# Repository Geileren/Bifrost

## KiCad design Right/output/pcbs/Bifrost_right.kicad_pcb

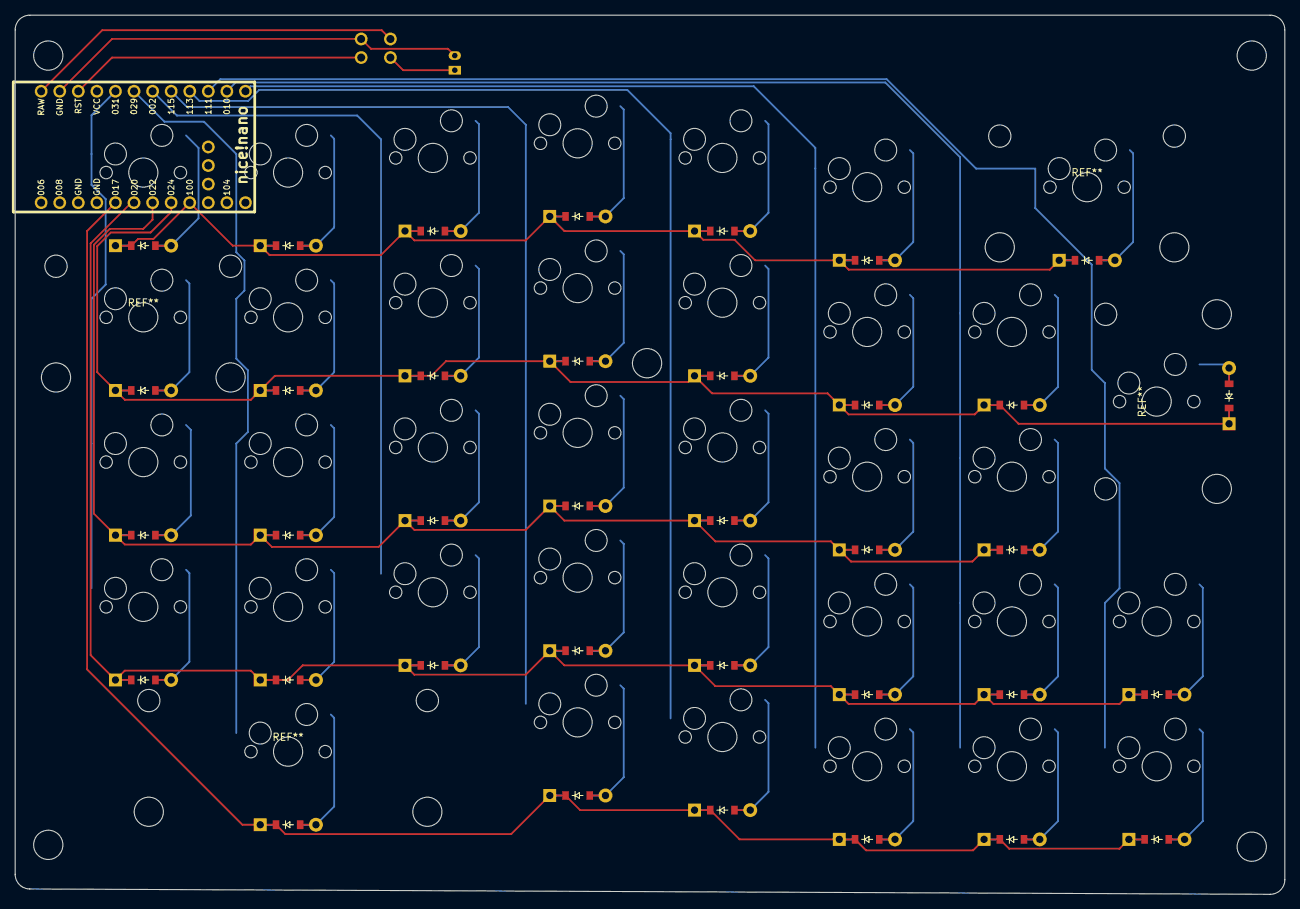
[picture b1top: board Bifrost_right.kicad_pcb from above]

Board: 2 copper layers, 173.7 x 120.2 mm, 76 parts (0 on the bottom side), 53 nets.

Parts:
D1, D2, D3, D4, D5, D6, D7, D8, D9, D10, D11, D12, D13, D14, D15, D16, D17, D18, D19, D20, D21, D22, D23, D24, D25, D26, D27, D28, D29, D30, D31, D32, D33, D34, D35, D36: ComboDiode
JST1: JST_PH_S2B-PH-K_02x2.00mm_Angled
MCU1: nice_nano
S1, S2, S3, S4, S5, S6, S7, S8, S9, S10, S11, S12, S13, S14, S15, S16, S17, S18, S19, S20, S21, S22, S23, S24, S25, S26, S27, S28, S29, S30, S31, S32, S33, S34, S35, S36: MX
SW1, SW2: switch_tht

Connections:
GND: JST1.2, MCU1.3, MCU1.4, MCU1.23, SW2.1
P002: MCU1.18, S10.1, S11.1, S12.1, S13.1
P009: MCU1.13, S24.1, S25.1, S26.1, S27.1, S28.1
P010: MCU1.14, S29.1, S30.1, S31.1, S32.1
P017: D5.1, D14.1, D19.1, D24.1, D29.1, D33.1, MCU1.5
P020: D1.1, D6.1, D10.1, D15.1, D20.1, D25.1, D30.1, D34.1, MCU1.6
P022: D2.1, D7.1, D11.1, D16.1, D21.1, D26.1, D31.1, MCU1.7
P024: D3.1, D8.1, D12.1, D17.1, D22.1, D27.1, D32.1, D35.1, MCU1.8
P029: MCU1.19, S5.1, S6.1, S7.1, S8.1, S9.1
P031: MCU1.20, S1.1, S2.1, S3.1, S4.1
P100: D4.1, D9.1, D13.1, D18.1, D23.1, D28.1, D36.1, MCU1.9
P111: MCU1.15, S33.1, S34.1, S35.1, S36.1
P113: MCU1.16, S19.1, S20.1, S21.1, S22.1, S23.1
P115: MCU1.17, S14.1, S15.1, S16.1, S17.1, S18.1
RAW: MCU1.24, SW1.2
RST: MCU1.22, SW2.2
c1_r1: D4.2, S4.2
c1_r2: D3.2, S3.2
c1_r3: D2.2, S2.2
c1_r4: D1.2, S1.2
c2_r1: D9.2, S9.2
c2_r2: D8.2, S8.2
c2_r3: D7.2, S7.2
c2_r4: D6.2, S6.2
c2_r5: D5.2, S5.2
c3_r1: D13.2, S13.2
c3_r2: D12.2, S12.2
c3_r3: D11.2, S11.2
c3_r4: D10.2, S10.2
c4_r1: D18.2, S18.2
c4_r2: D17.2, S17.2
c4_r3: D16.2, S16.2
c4_r4: D15.2, S15.2
c4_r5: D14.2, S14.2
c5_r1: D23.2, S23.2
c5_r2: D22.2, S22.2
c5_r3: D21.2, S21.2
c5_r4: D20.2, S20.2
c5_r5: D19.2, S19.2
c6_r1: D28.2, S28.2
c6_r2: D27.2, S27.2
c6_r3: D26.2, S26.2
c6_r4: D25.2, S25.2
c6_r5: D24.2, S24.2
c7_r2: D32.2, S32.2
c7_r3: D31.2, S31.2
c7_r4: D30.2, S30.2
c7_r5: D29.2, S29.2
c8_r1: D36.2, S36.2
c8_r2: D35.2, S35.2
c8_r4: D34.2, S34.2
c8_r5: D33.2, S33.2
pos: JST1.1, SW1.1

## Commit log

2026-03-24 initial commit. layout for left
2026-03-24 adds layout img for right side
2026-03-24 finish left PCB layout. Needs wires and stabs
2026-03-28 finish left?
2026-03-28 added stabs to left
